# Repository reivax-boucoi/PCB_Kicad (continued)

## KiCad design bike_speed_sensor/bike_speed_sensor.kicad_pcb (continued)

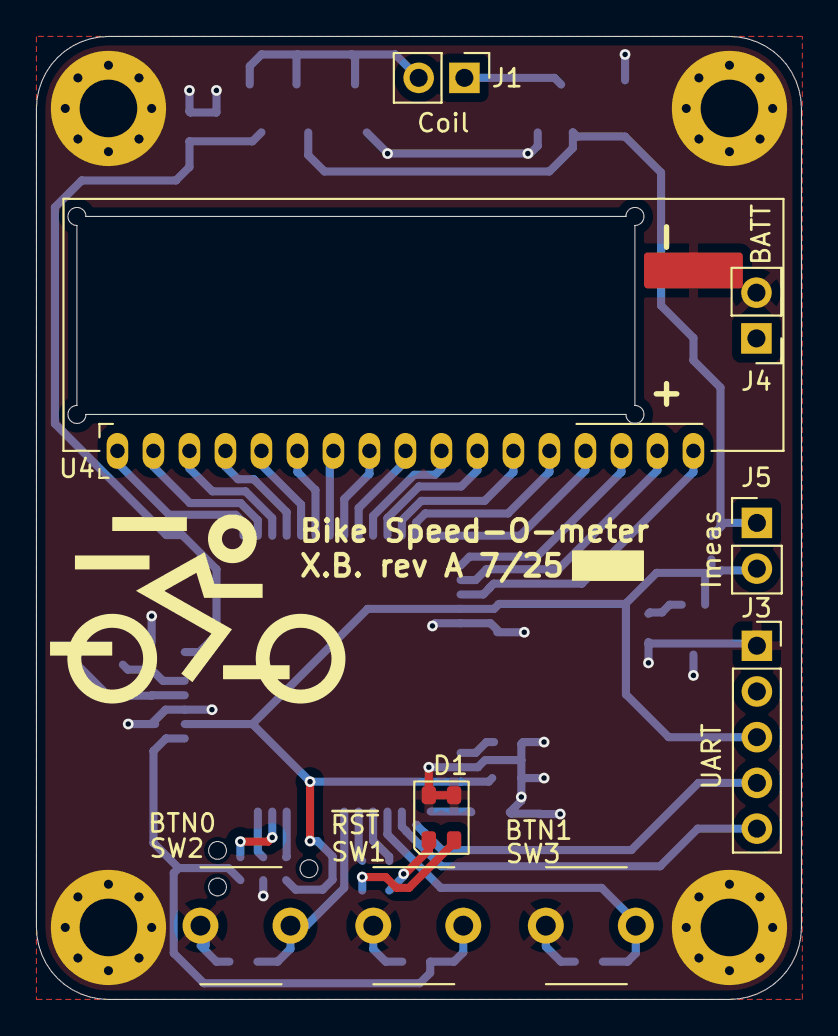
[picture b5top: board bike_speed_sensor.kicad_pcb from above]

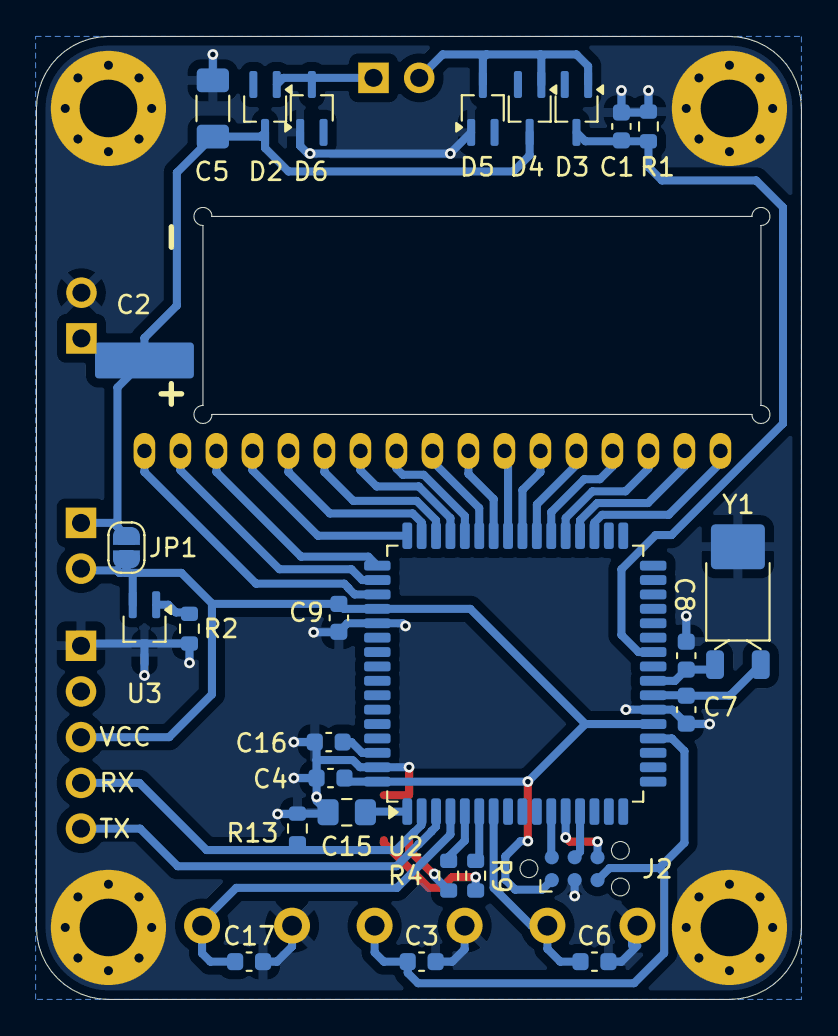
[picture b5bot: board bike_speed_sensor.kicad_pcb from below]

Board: 2 copper layers, 42.5 x 53.5 mm, 40 parts (27 on the bottom side), 40 nets.

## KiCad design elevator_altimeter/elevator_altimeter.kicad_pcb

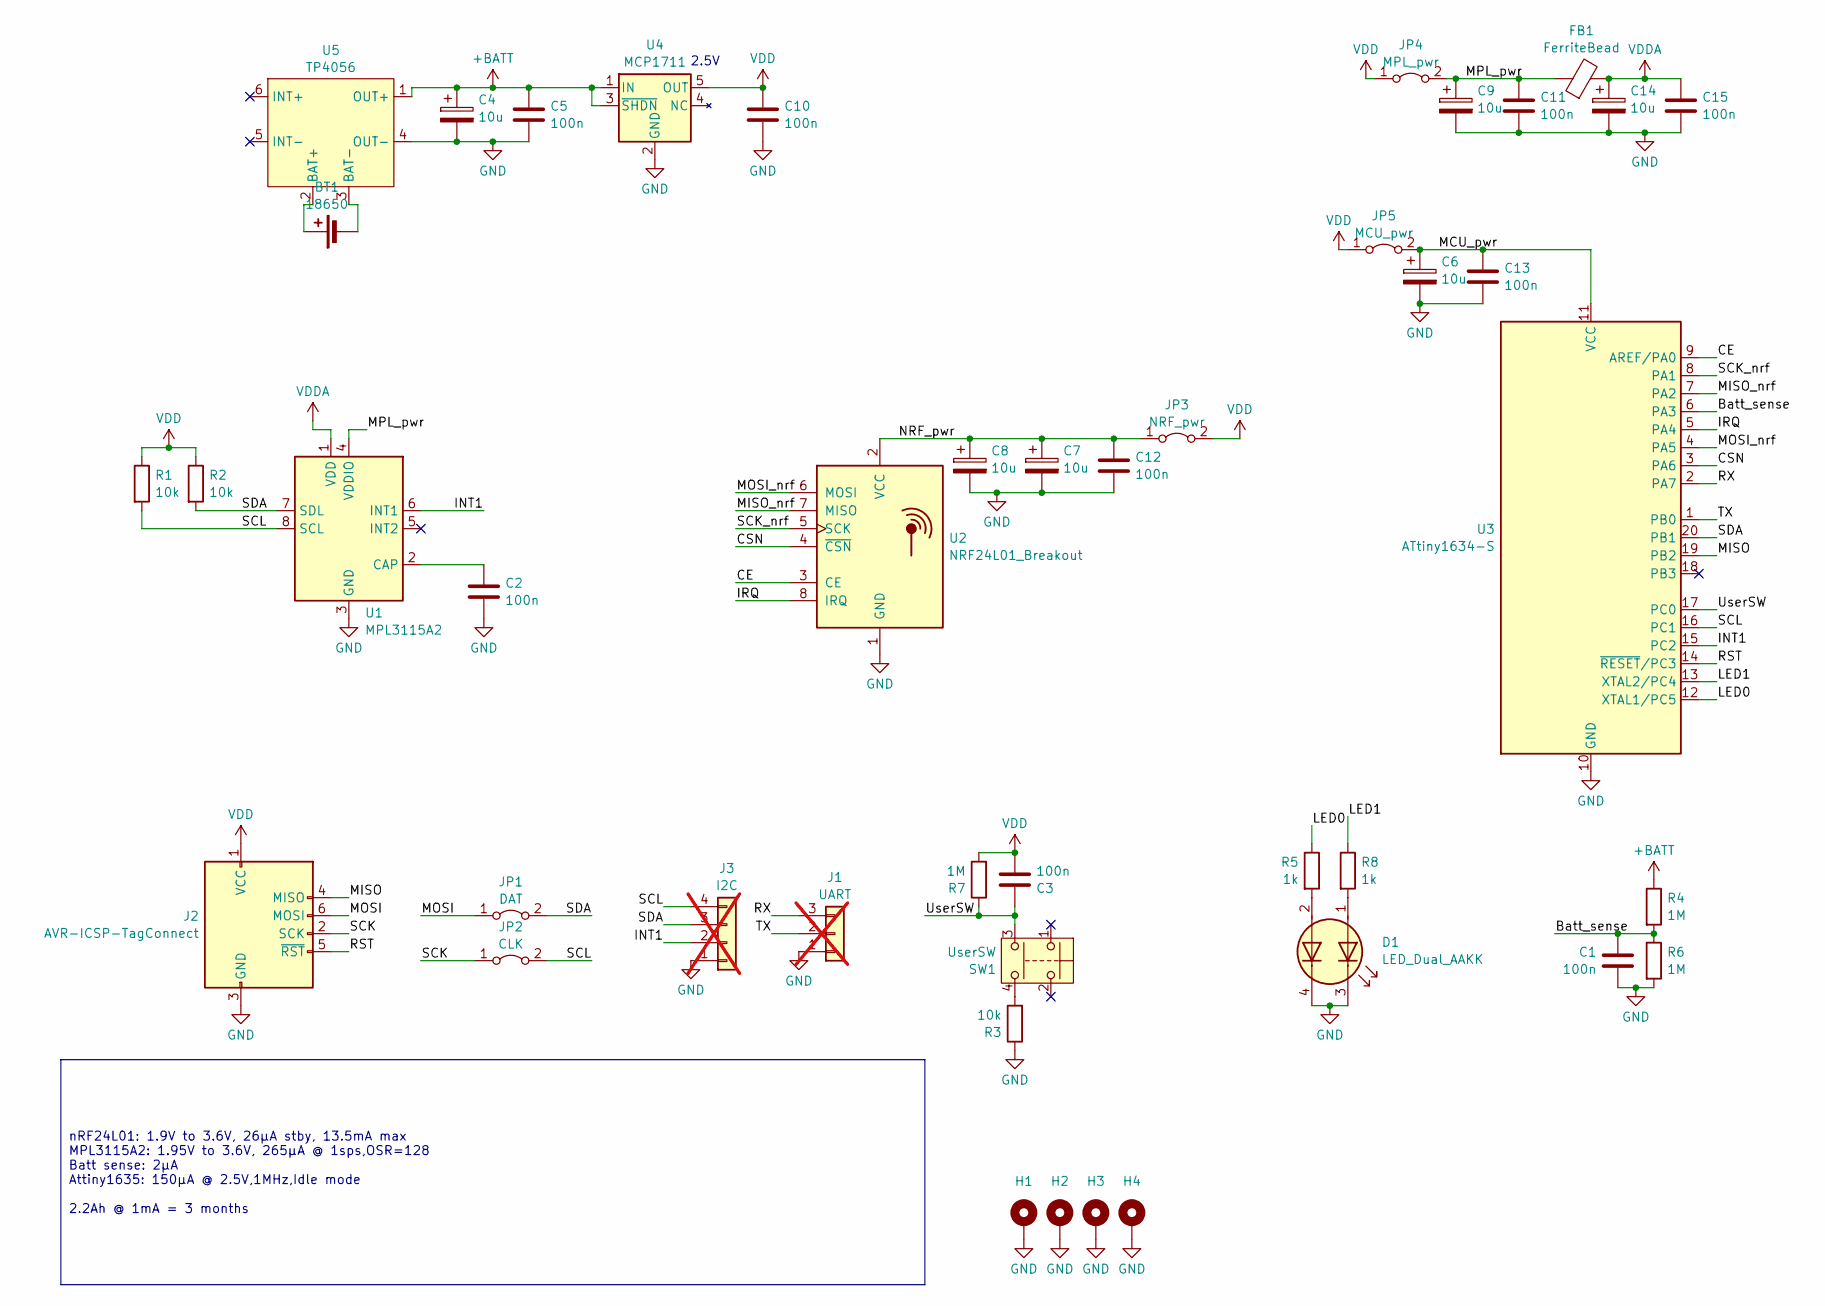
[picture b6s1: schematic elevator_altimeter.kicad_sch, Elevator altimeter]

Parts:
BT1: 18650; BatteryHolder_Keystone_1042_1x18650
C1, C2, C3, C5, C10, C11, C12, C13, C15: 100n; C_0603_1608Metric_Pad1.08x0.95mm_HandSolder
C4, C6, C7, C8, C9, C14: 10u; C_0805_2012Metric_Pad1.18x1.45mm_HandSolder
D1: LED_Dual_AAKK; LED_Cree-PLCC4_3.2x2.8mm_CCW
FB1: FerriteBead; L_0805_2012Metric_Pad1.05x1.20mm_HandSolder
H1, H2, H3, H4: MountingHole_3.2mm_M3_Pad_Via
J1: UART; PinHeader_1x03_P2.54mm_Vertical; not fitted
J2: AVR-ICSP-TagConnect; Tag-Connect_TC2030-IDC-NL_2x03_P1.27mm_Vertical
J3: I2C; PinHeader_1x04_P2.54mm_Vertical; not fitted
JP1: DAT; SolderJumper-2_P1.3mm_Bridged_RoundedPad1.0x1.5mm
JP2: CLK; SolderJumper-2_P1.3mm_Bridged_RoundedPad1.0x1.5mm
JP3: NRF_pwr; SolderJumper-2_P1.3mm_Bridged_RoundedPad1.0x1.5mm
JP4: MPL_pwr; SolderJumper-2_P1.3mm_Bridged_RoundedPad1.0x1.5mm
JP5: MCU_pwr; SolderJumper-2_P1.3mm_Bridged_RoundedPad1.0x1.5mm
R1, R2, R3: 10k; R_0603_1608Metric_Pad0.98x0.95mm_HandSolder
R4, R6, R7: 1M; R_0603_1608Metric_Pad0.98x0.95mm_HandSolder
R5, R8: 1k; R_0603_1608Metric_Pad0.98x0.95mm_HandSolder
SW1: UserSW; Push_E-Switch_KS01Q01
U1: MPL3115A2; NXP_LGA-8_3x5mm_P1.25mm_H1.1mm
U2: NRF24L01_Breakout; nRF24L01_Breakout
U3: ATtiny1634-S; SOIC-20W_7.5x12.8mm_P1.27mm
U4: MCP1711; SOT-23-5
U5: TP4056; TP4056_USB-C_module

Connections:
+BATT: C4.1, C5.1, R4.1, U4.1 (IN), U4.3 (~SHDN), U5.1 (OUT+)
/Batt_sense: C1.1, R4.2, R6.1, U3.6 (PA3)
/CE: U2.3 (CE), U3.9 (AREF/PA0)
/CSN: U2.4 (~CSN), U3.3 (PA6)
/INT1: J3.2, U1.6 (INT1), U3.15 (PC2)
/IRQ: U2.8 (IRQ), U3.5 (PA4)
/LED0: R5.1, U3.12 (XTAL1/PC5)
/LED1: R8.1, U3.13 (XTAL2/PC4)
/MCU_pwr: C6.1, C13.1, JP5.2 (B), U3.11 (VCC)
/MISO: J2.4 (MISO), U3.19 (PB2)
/MISO_nrf: U2.7 (MISO), U3.7 (PA2)
/MOSI: J2.6 (MOSI), JP1.1 (A)
/MOSI_nrf: U2.6 (MOSI), U3.4 (PA5)
/MPL_pwr: C9.1, C11.1, FB1.1, JP4.2 (B), U1.4 (VDDIO)
/NRF_pwr: C7.1, C8.1, C12.1, JP3.1 (A), U2.2 (VCC)
/RST: J2.5 (~RST), U3.14 (~RESET/PC3)
/RX: J1.3, U3.2 (PA7)
/SCK: J2.2 (SCK), JP2.1 (A)
/SCK_nrf: U2.5 (SCK), U3.8 (PA1)
/SCL: J3.4, JP2.2 (B), R1.2, U1.8 (SCL), U3.16 (PC1)
/SDA: J3.3, JP1.2 (B), R2.2, U1.7 (SDL), U3.20 (PB1)
/TX: J1.2, U3.1 (PB0)
/UserSW: C3.1, R7.1, SW1.3, U3.17 (PC0)
GND: C1.2, C2.2, C4.2, C5.2, C6.2, C7.2, C8.2, C9.2, C10.2, C11.2, C12.2, C13.2, C14.2, C15.2, D1.3 (K1), D1.4 (K2), H1.1, H2.1, H3.1, H4.1, J1.1, J2.3 (GND), J3.1, R3.1, R6.2, U1.3 (GND), U2.1 (GND), U3.10 (GND), U4.2 (GND), U5.4 (OUT-)
unnamed: BT1.1 (+), U5.2 (BAT+)
unnamed: BT1.2 (-), U5.3 (BAT-)
unnamed: D1.1 (A1), R8.2
unnamed: D1.2 (A2), R5.2
unnamed: R3.2, SW1.4
unnamed: C2.1, U1.2 (CAP)
VDD: C3.2, C10.1, J2.1 (VCC), JP3.2 (B), JP4.1 (A), JP5.1 (A), R1.1, R2.1, R7.2, U4.5 (OUT)
VDDA: C14.1, C15.1, FB1.2, U1.1 (VDD)

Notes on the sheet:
nRF24L01: 1.9V to 3.6V, 26µA stby, 13.5mA max MPL3115A2: 1.95V to 3.6V, 265µA @ 1sps,OSR=128 Batt sense: 2µA Attiny1635: 150µA @ 2.5V,1MHz,Idle mode 2.2Ah @ 1mA = 3 months
2.5V

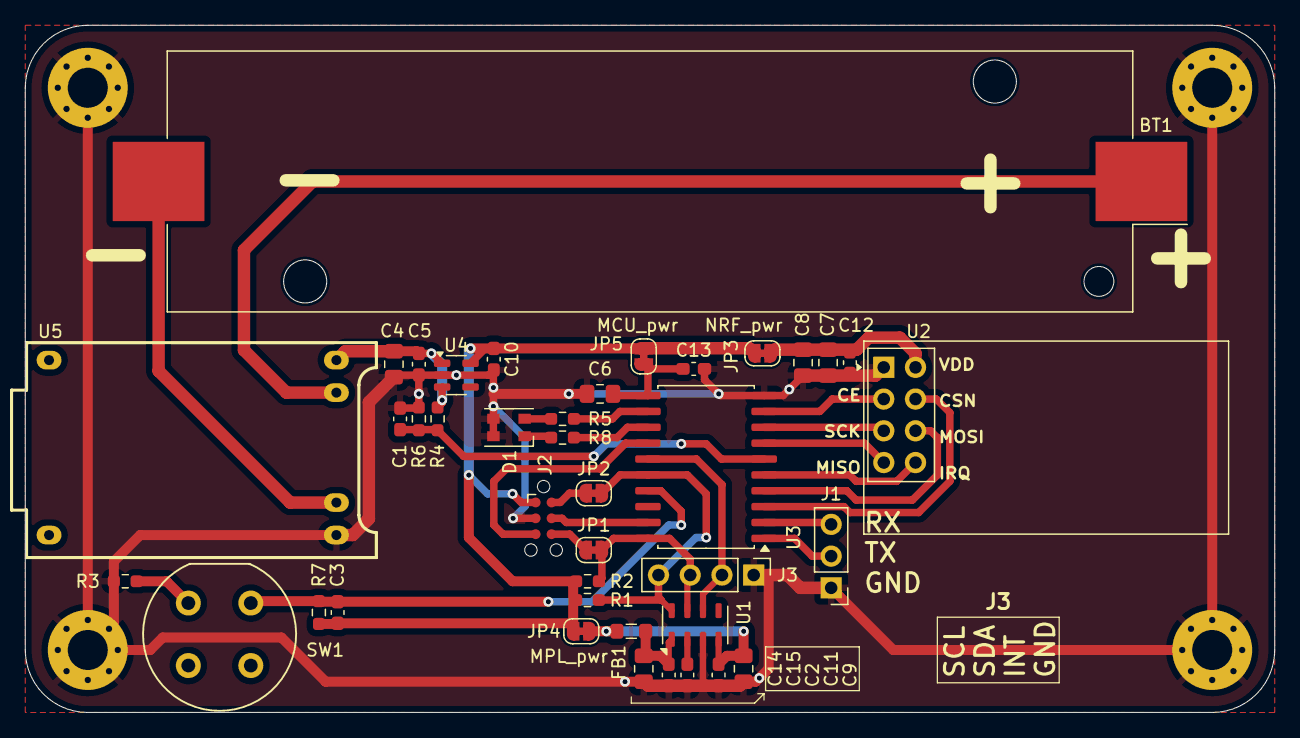
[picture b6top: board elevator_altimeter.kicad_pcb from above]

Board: 2 copper layers, 100.0 x 55.0 mm, 44 parts (0 on the bottom side), 32 nets.

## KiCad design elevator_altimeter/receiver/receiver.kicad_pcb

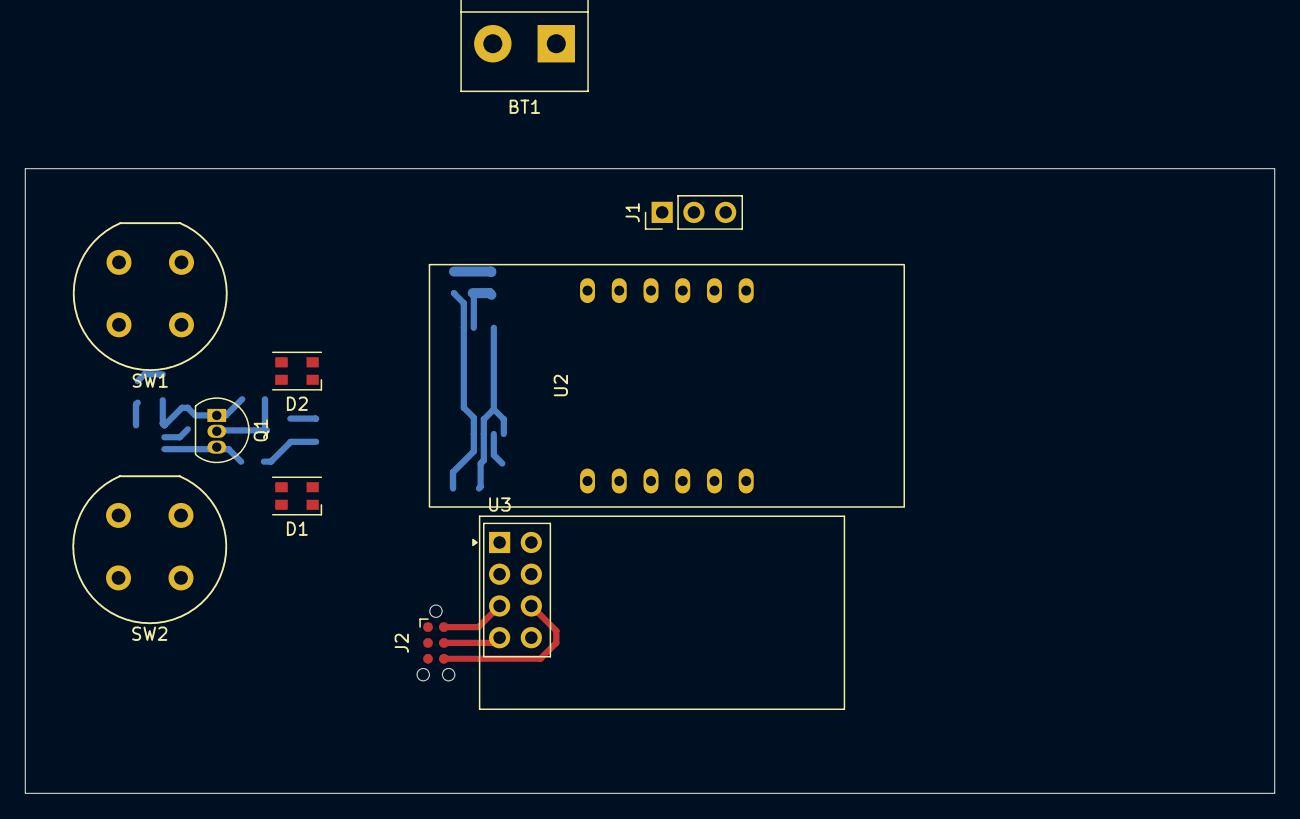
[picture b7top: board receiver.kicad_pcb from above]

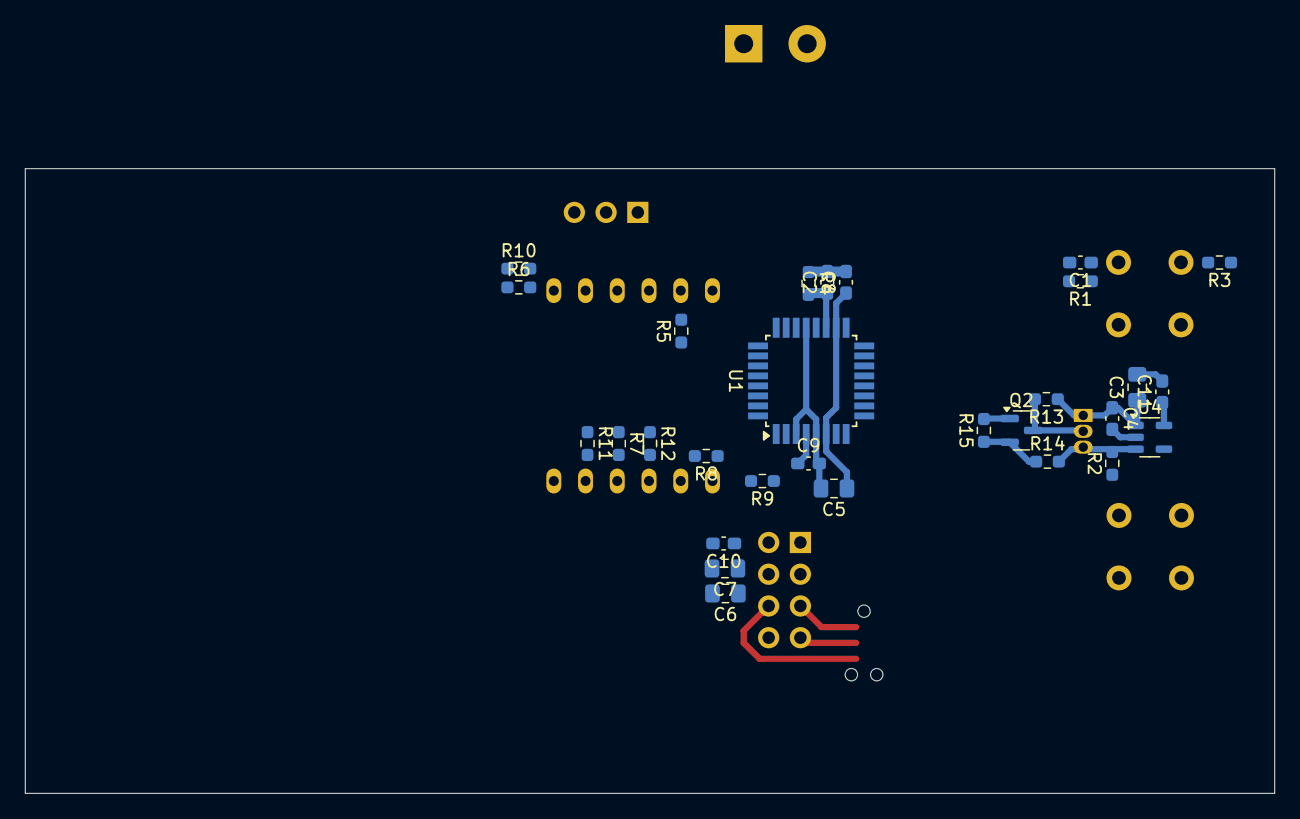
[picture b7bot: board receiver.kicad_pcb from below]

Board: 2 copper layers, 100.0 x 50.0 mm, 39 parts (29 on the bottom side), 36 nets.

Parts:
BT1: 18650; TerminalBlock_bornier-2_P5.08mm
C1, C2, C4, C8, C9, C10, C11: 100n; C_0603_1608Metric_Pad1.08x0.95mm_HandSolder
C3, C5, C6, C7: 10u; C_0805_2012Metric_Pad1.18x1.45mm_HandSolder
D1, D2: LED_Dual_AAKK; LED_Cree-PLCC4_3.2x2.8mm_CCW
J1: UART; PinHeader_1x03_P2.54mm_Vertical
J2: AVR-ICSP-TagConnect; Tag-Connect_TC2030-IDC-NL_2x03_P1.27mm_Vertical
Q1: TP0606; TO-92L_Inline
Q2: 2N7002; SOT-23
R1: 1M; R_0603_1608Metric_Pad0.98x0.95mm_HandSolder
R2, R3, R4, R13, R14, R15: 39k; R_0603_1608Metric_Pad0.98x0.95mm_HandSolder
R5, R6, R7, R8, R9, R10, R11, R12: 470; R_0603_1608Metric_Pad0.98x0.95mm_HandSolder
SW1: UserSW; Push_E-Switch_KS01Q01
SW2: PWR_SW; Push_E-Switch_KS01Q01
U1: ATmega8-16A; TQFP-32_7x7mm_P0.8mm
U2: 5631AH-S_3digit_7segment_display
U3: NRF24L01_Breakout; nRF24L01_Breakout
U4: MCP1711; SOT-23-5

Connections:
+BATT: BT1.1 (+), C3.1, C4.1, Q1.1 (S), R13.1, U4.1 (IN)
/A: R5.1, U1.11 (PD7)
/B: R6.1, U1.10 (PD6)
/Batt_en: Q1.3 (D), R2.2, R14.2, U4.3 (~SHDN)
/Batt_sense: C2.1, R2.1, R4.2, U1.19 (ADC6)
/C: R7.1, U1.9 (PD5)
/CE: U1.13 (PB1), U3.3 (CE)
/CSN: U1.12 (PB0), U3.4 (~CSN)
/D: R8.1, U1.2 (PD4)
/DIG1: U1.25 (PC2), U2.12 (CC1)
/DIG2: U1.26 (PC3), U2.9 (CC2)
/DIG3: U1.27 (PC4), U2.8 (CC3)
/DIG4: D1.3 (K1), D1.4 (K2), D2.3 (K1), D2.4 (K2), U1.28 (PC5)
/DP: R12.1, U1.30 (PD0)
/E: R9.1, U1.1 (PD3)
/F: R10.1, U1.32 (PD2)
/G: R11.1, U1.31 (PD1)
/IRQ: U1.14 (PB2), U3.8 (IRQ)
/MISO: J2.4 (MISO), U1.16 (PB4), U3.7 (MISO)
/MOSI: J2.6 (MOSI), U1.15 (PB3), U3.6 (MOSI)
/PWR_EN: Q2.1 (G), R15.2, U1.23 (PC0)
/RST: J2.5 (~RST), U1.29 (PC6/~RESET)
/SCK: J2.2 (SCK), U1.17 (PB5), U3.5 (SCK)
/UserSW: C1.1, R1.1, SW1.3, U1.24 (PC1)
GND: BT1.2 (-), C2.2, C3.2, C4.2, C5.2, C6.2, C7.2, C8.2, C9.2, C10.2, C11.2, J1.1, J2.3 (GND), Q2.2 (S), R3.1, R4.1, R14.1, R15.1, SW2.2, U1.3 (GND), U1.5 (GND), U1.21 (AGND), U3.1 (GND), U4.2 (GND)
unnamed: D1.1 (A1), R10.2, U2.10 (f)
unnamed: D1.2 (A2), R9.2, U2.1 (e)
unnamed: D2.1 (A1), R12.2, U2.3 (DPX)
unnamed: D2.2 (A2), R11.2, U2.5 (g)
unnamed: Q1.2 (G), Q2.3 (D), R13.2, SW2.1
unnamed: R3.2, SW1.4
unnamed: R5.2, U2.11 (a)
unnamed: R6.2, U2.7 (b)
unnamed: R7.2, U2.4 (c)
unnamed: R8.2, U2.2 (d)
VDD: C1.2, C5.1, C6.1, C7.1, C8.1, C9.1, C10.1, C11.1, J2.1 (VCC), R1.2, U1.4 (VCC), U1.6 (VCC), U1.18 (AVCC), U3.2 (VCC), U4.5 (OUT)

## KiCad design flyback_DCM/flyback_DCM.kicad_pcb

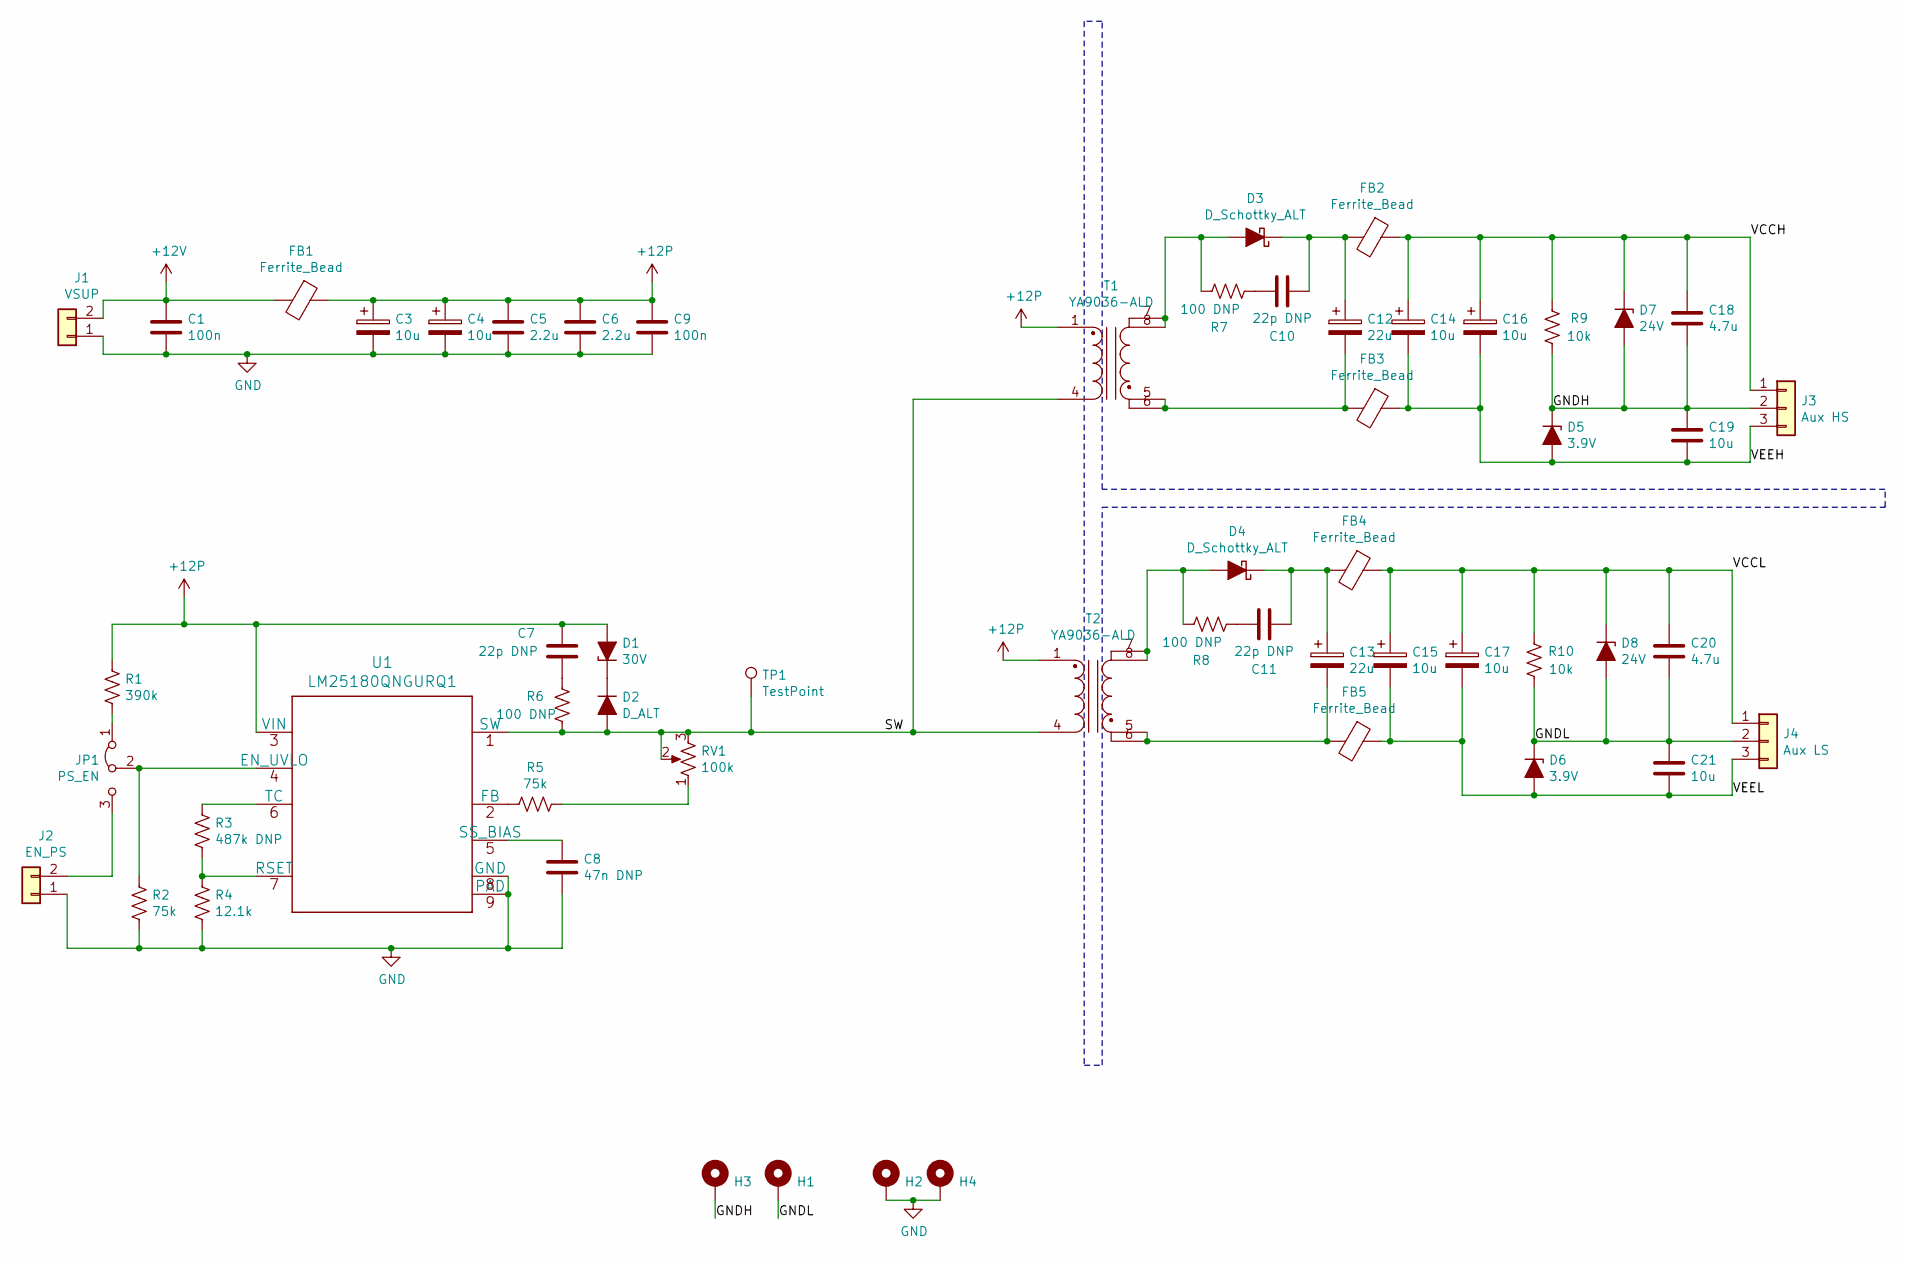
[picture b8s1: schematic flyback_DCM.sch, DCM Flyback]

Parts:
C1, C9: 100n; C_0805_2012Metric
C3, C4, C14, C15, C16, C17: 10u; C_1206_3216Metric
C5, C6: 2.2u; C_0805_2012Metric
C7, C10, C11: 22p DNP; C_0805_2012Metric
C8: 47n DNP; C_0805_2012Metric
C12, C13: 22u; C_1210_3225Metric
C18, C20: 4.7u; C_0805_2012Metric
C19, C21: 10u; C_0805_2012Metric
D1: 30V; D_SMA
D2: D_ALT; D_SOD-123
D3, D4: D_Schottky_ALT; D_SOD-123
D5, D6: 3.9V; D_SOD-123
D7, D8: 24V; D_SOD-323
FB1: Ferrite_Bead; L_1206_3216Metric
FB2, FB3, FB4, FB5: Ferrite_Bead; L_0603_1608Metric
H1, H2, H3, H4: MountingHole_Pad; MountingHole_2.2mm_M2_Pad_Via
J1: VSUP; PinSocket_1x02_P2.54mm_Vertical
J2: EN_PS; PinSocket_1x02_P2.54mm_Vertical
J3: Aux HS; PinHeader_1x03_P2.54mm_Vertical
J4: Aux LS; PinHeader_1x03_P2.54mm_Vertical
JP1: PS_EN; SolderJumper-3_P1.3mm_Bridged12_RoundedPad1.0x1.5mm
R1: 390k; R_0603_1608Metric
R2, R5: 75k; R_0603_1608Metric
R3: 487k DNP; R_0603_1608Metric
R4: 12.1k; R_0603_1608Metric
R6, R7, R8: 100 DNP; R_0805_2012Metric
R9, R10: 10k; R_0805_2012Metric
RV1: 100k; Potentiometer_Bourns_3224W_Vertical
T1, T2: YA9036-ALD
TP1: TestPoint; TestPoint_Keystone_5010-5014_Multipurpose
U1: LM25180QNGURQ1

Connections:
+12P: C3.1, C4.1, C5.1, C6.1, C7.2, C9.1, D1.2 (A), FB1.1, R1.1, T1.1 (AA), T2.1 (AA), U1.3 (VIN)
+12V: C1.1, FB1.2, J1.2
/GNDH: C18.2, C19.1, D5.1 (K), D7.2 (A), H3.1, J3.2, R9.1
/GNDL: C20.2, C21.1, D6.1 (K), D8.2 (A), H1.1, J4.2, R10.1
/SW: D2.2 (A), R6.2, RV1.2, RV1.3, T1.4 (AB), T2.4 (AB), TP1.1, U1.1 (SW)
/VCCH: C14.1, C16.1, C18.1, D7.1 (K), FB2.1, J3.1, R9.2
/VCCL: C15.1, C17.1, C20.1, D8.1 (K), FB4.1, J4.1, R10.2
/VEEH: C14.2, C16.2, C19.2, D5.2 (A), FB3.1, J3.3
/VEEL: C15.2, C17.2, C21.2, D6.2 (A), FB5.1, J4.3
GND: C1.2, C3.2, C4.2, C5.2, C6.2, C8.2, C9.2, H2.1, H4.1, J1.1, J2.1, R2.2, R4.2, U1.8 (GND), U1.9 (PAD), U1.V
unnamed: C7.1, R6.1
unnamed: C8.1, U1.5 (SS_BIAS)
unnamed: C10.1, C12.1, D3.1 (K), FB2.2
unnamed: C10.2, R7.2
unnamed: C11.1, C13.1, D4.1 (K), FB4.2
unnamed: C11.2, R8.2
unnamed: C12.2, FB3.2, T1.5 (SA), T1.6 (SAA)
unnamed: C13.2, FB5.2, T2.5 (SA), T2.6 (SAA)
unnamed: D1.1 (K), D2.1 (K)
unnamed: D3.2 (A), R7.1, T1.7 (SAB), T1.8 (SB)
unnamed: D4.2 (A), R8.1, T2.7 (SAB), T2.8 (SB)
unnamed: J2.2, JP1.3 (B)
unnamed: JP1.1 (A), R1.2
unnamed: JP1.2 (C), R2.1, U1.4 (EN_UVLO)
unnamed: R3.1, U1.6 (TC)
unnamed: R3.2, R4.1, U1.7 (RSET)
unnamed: R5.1, RV1.1
unnamed: R5.2, U1.2 (FB)

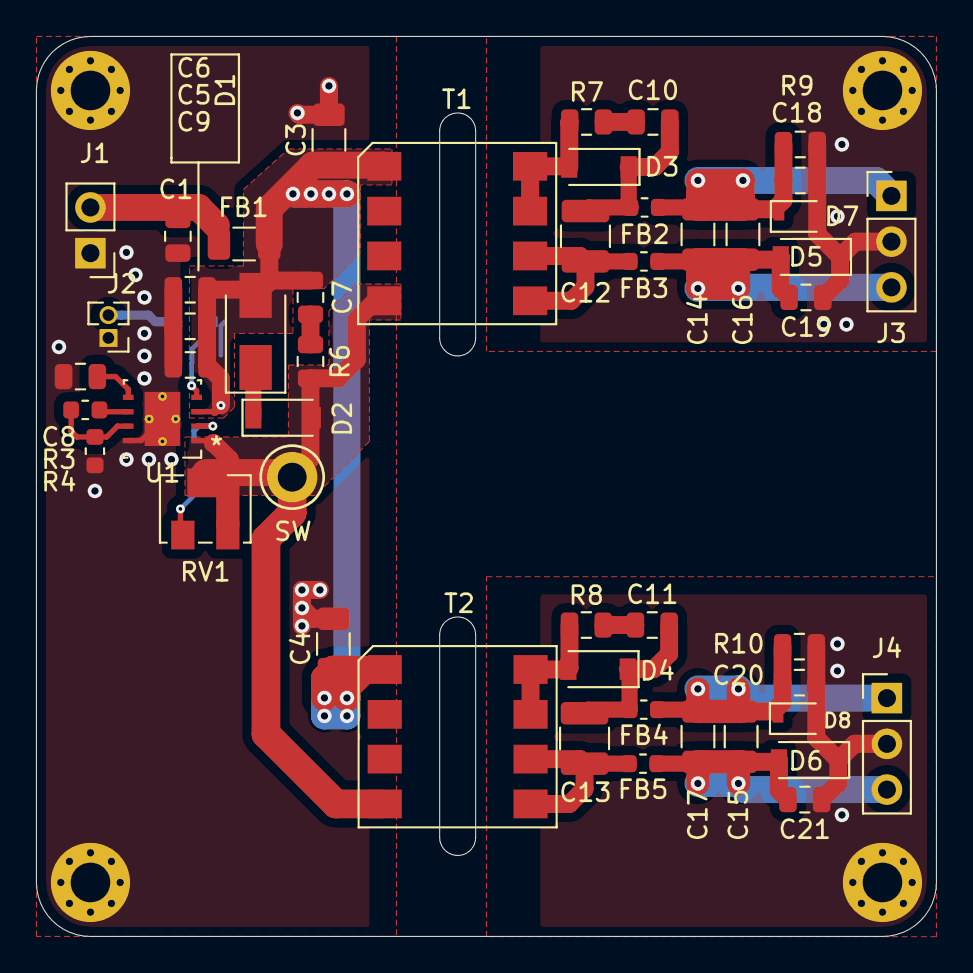
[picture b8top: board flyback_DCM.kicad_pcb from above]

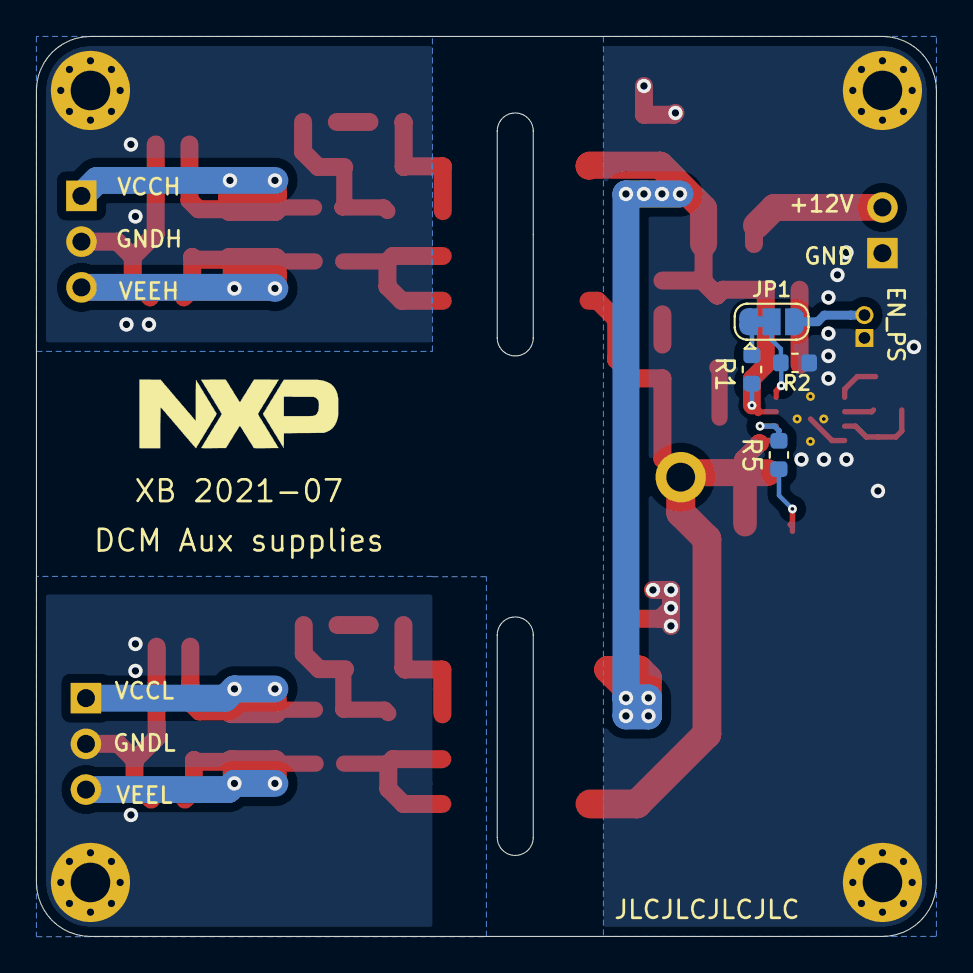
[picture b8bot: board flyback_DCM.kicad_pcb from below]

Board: 4 copper layers, 50.0 x 50.0 mm, 57 parts (4 on the bottom side), 28 nets.
